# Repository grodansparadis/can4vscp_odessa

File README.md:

<h1>Odessa general CAN4VSCP module</h1>

This module is part of the [VSCP project](https://www.vscp.org).  It is free to use, modify and sell. The only thing we kindly ask is that improvements and extensions are contributed back to the project (at your will). This to make the project better for everyone. All design files is licensed under the [MIT license](https://en.wikipedia.org/wiki/MIT_License).

## Abstract

This document describes the Odessa CAN4VSCP module, its functionality, and usage.
The module is a general-purpose module that connects to a CAN4VSCP bus and can read digital inputs, A/D inputs, and control digital outputs and more. Its functionality is exposed over a 24 pin connector that can be used to connect sensors and actuators.

TRhe module is constructed to be used for custom projects where you need a CAN4VSCP interface to read sensors and control actuators. It can be used in home automation, industrial control, remote monitoring, and more. The module is based on a PIC18F26K83 microcontroller with built-in CAN and A/D converters. It has 8 digital inputs, 4 digital outputs, and 4 A/D inputs. The digital inputs can be used to read switches, buttons, or other digital signals. The digital outputs can be used to control relays, LEDs, or other actuators. The A/D inputs can be used to read analog sensors such as temperature sensors, light sensors, or potentiometers.

Firmware is available that give the module a general I/O functionality. This firmware can be used as a starting point for your own projects.

The module can be attached to a standard DIN Rail or be mounted directly on a wall. 
The module fully adopts to the CAN4VSCP specification and can be powered directly over the bus with a 9-28V DC power source. It has a rich register set for configuration and any information events defined. It also have a decision matrix for easy dynamic event handling.

VSCP CAN modules are designed to work on a VSCP4CAN bus which use ordinary RJ-45 connectors and is powered with 9-30V DC over the same cable. This means there is no need for a separate power cable. All that is needed is a CAT5 or better twisted pair cable. Bus length can be a maximum of 500 meters with drops of maximum 24 meters length (up to a total of 120 meters). As for all VSCP4CAN modules the communication speed is fixed at 125 kbps.

All VSCP modules contains information of there own setup, manual, hardware version, manufacturer etc. You just ask the module for the information you need and you will get it. When they are started up they have a default functionality that often is all that is needed to get a working setup. If the module have something to report it will send you an event and if it is setup to react on a certain type of event it will do it's work when you send event(s) to it.

<hr>

---

## Project files

### User manual
  * [User Manual](https://grodansparadis.github.io/can4vscp-odessa/#)

### Schematic, PCB, 3D files etc
  * [Schematics reversion A](https://github.com/grodansparadis/can4vscp-odessa/blob/master/eagle/odessa_sch_rev_a.png)
  * Hardware design files is made in [KiCad](https://kicad.org) and can be found in the `kicad` directory. Valid from reversion A of the hardware.
  * Gerber files for PCB production can be found in the `gerber` directory (in the `kicad` folder).
  * Eagle schema and board files for reversion A and B can be found in the `eagle` directory. They are no longer actively updated.

 ### Firmware

 The firmware is developed in [MPLAB X IDE](https://www.microchip.com/mplab/mplab-x-ide) using the [XC8 compiler](https://www.microchip.com/mplab/compilers).

  * Binary release files is available [here](https://github.com/grodansparadis/can4vscp-odessa/releases)

### MDF - Module Description File(s)
  * [MDF file version: 1 Release date: 2020-05-15](http://www.eurosource.se/odessa001.xml)

### Support
If you need support, please open an issue in the [GitHub repository](https://github.com/grodansparadis/can4vscp-odessa/issues).

### Buy a ready made modules
You can buy a ready made module from [Grodans Paradis](http://www.grodansparadis.com).

### Project related links
  * [VSCP project](https://www.vscp.org)
  * [VSCP Documentation site](https://docs.vscp.org/)
  * [VSCP Wiki](https://github.com/grodansparadis/vscp/wiki)

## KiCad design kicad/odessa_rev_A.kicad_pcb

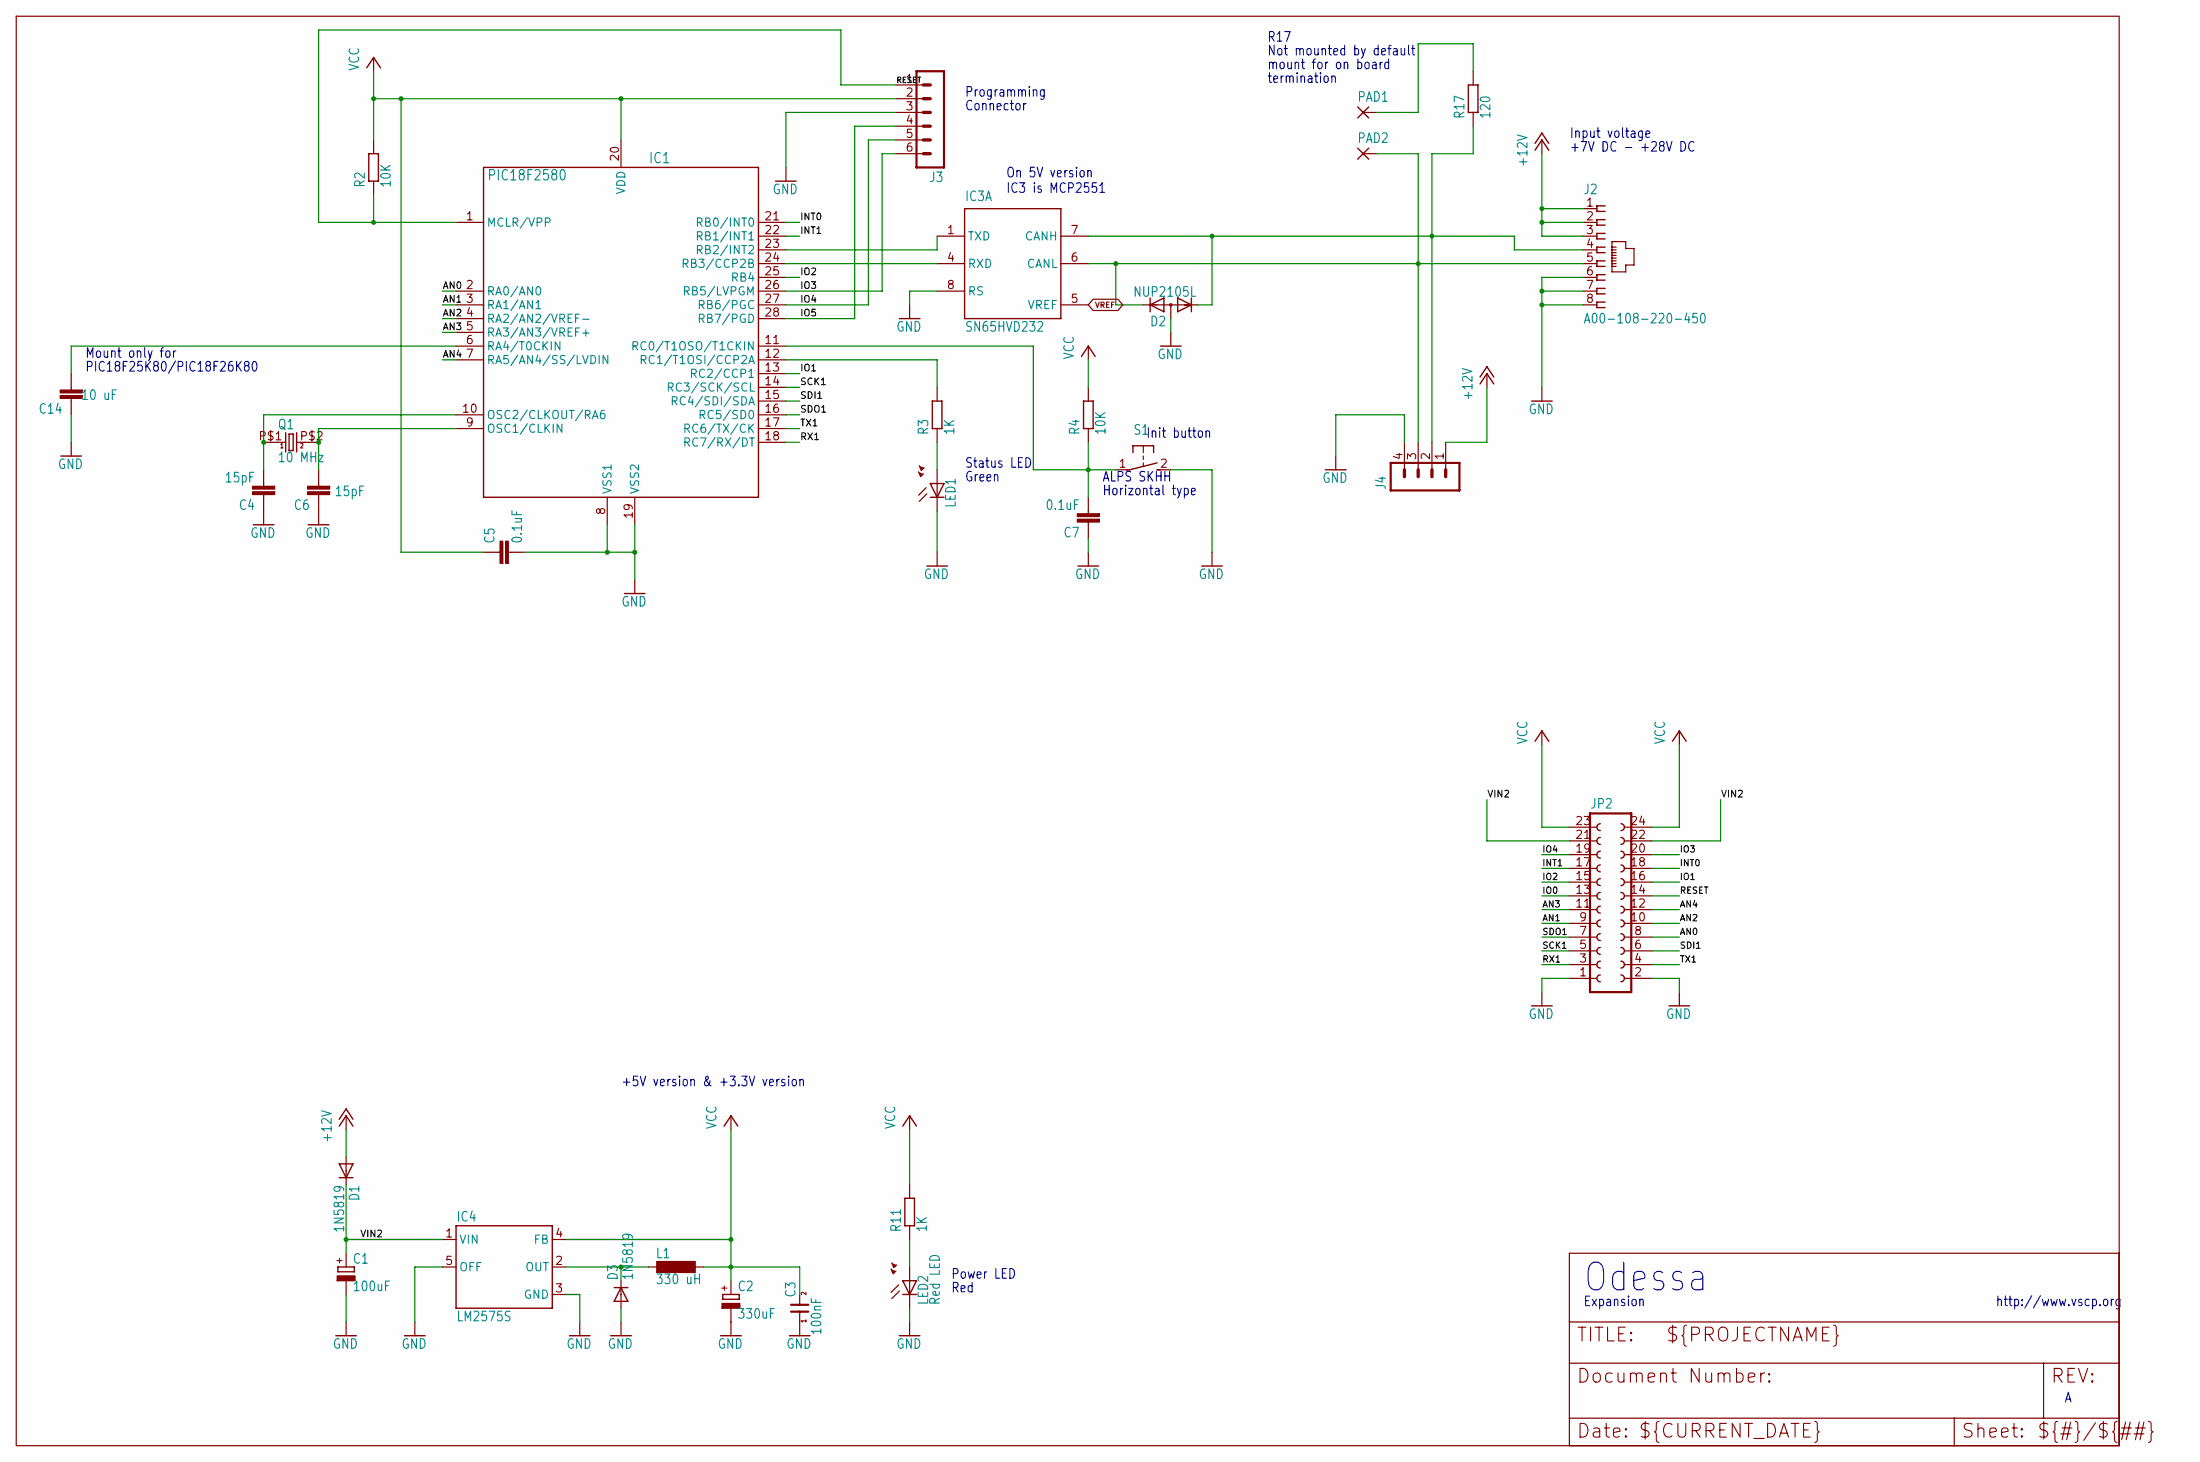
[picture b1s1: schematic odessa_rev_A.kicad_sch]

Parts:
C1: 100uF; PANASONIC_D
C2: 330uF; PANASONIC_D
C3: 100nF; 0805
C4, C6: 15pF; C0805
C5, C7: 0.1uF; C0805
C14: 10 uF; C0805
D1, D3: 1N5819; SOD123
D2: NUP2105L; SOT23
IC1: PIC18F2580; SO28
IC3: SN65HVD232; SO-08
IC4: LM2575S; TO263-5
J2: A00-108-220-450; RJ-45
J3: MA06-1
J4: MA04-1
JP2: FE12-2
L1: 330 uH; DO3316P
LED1: LEDCHIP-LED0805; CHIP-LED0805
LED2: Red LED; CHIP-LED0805
PAD1, PAD2: 1,6/0,8; 1,6_0,8
Q1: 10 MHz; 9C
R2, R4: 10K; R0805
R3, R11: 1K; R0805
R17: 120; R0805
S1: 31-XX; B3F-31XX

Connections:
+12V: D1.A, J2.1, J2.2, J2.3, J4.1
AN0: IC1.2 (RA0/AN0), JP2.8
AN1: IC1.3 (RA1/AN1), JP2.9
AN2: IC1.4 (RA2/AN2/VREF-), JP2.10
AN3: IC1.5 (RA3/AN3/VREF+), JP2.11
AN4: IC1.7 (RA5/AN4/SS/LVDIN), JP2.12
CANL: D2.2 (K2), IC3.6 (CANL), J2.5, J4.3, PAD2.1
GND: C1.-, C2.-, C3.1, C4.1, C5.2, C6.1, C7.1, C14.1, D2.3 (A), D3.A, IC1.8 (VSS1), IC1.19 (VSS2), IC3.2 (VSS), IC3.8 (RS), IC4.3 (GND), IC4.5 (OFF), J2.6, J2.7, J2.8, J3.3, J4.4, JP2.1, JP2.2, LED1.C, LED2.C, S1.2 (S)
INT0: IC1.21 (RB0/INT0), JP2.18
INT1: IC1.22 (RB1/INT1), JP2.17
IO0: JP2.13
IO1: IC1.13 (RC2/CCP1), JP2.16
IO2: IC1.25 (RB4), JP2.15
IO3: IC1.26 (RB5/LVPGM), J3.6, JP2.20
IO4: IC1.27 (RB6/PGC), J3.5, JP2.19
IO5: IC1.28 (RB7/PGD), J3.4
unnamed: D3.C, IC4.2 (OUT), L1.1
unnamed: C4.2, IC1.10 (OSC2/CLKOUT/RA6), Q1.P$1 (1)
unnamed: C14.2, IC1.6 (RA4/T0CKIN)
unnamed: IC1.12 (RC1/T1OSI/CCP2A), R3.2
unnamed: LED1.A, R3.1
unnamed: C7.2, IC1.11 (RC0/T1OSO/T1CKIN), R4.1, S1.1
unnamed: C6.2, IC1.9 (OSC1/CLKIN), Q1.P$2 (2)
unnamed: PAD1.1, R17.2
unnamed: LED2.A, R11.1
unnamed: D2.1 (K1), IC3.7 (CANH), J2.4, J4.2, R17.1
RESET: IC1.1 (MCLR/VPP), J3.1, JP2.14, R2.1
RX1: IC1.18 (RC7/RX/DT), JP2.3
RXCAN: IC1.24 (RB3/CCP2B), IC3.4 (RXD)
SCK1: IC1.14 (RC3/SCK/SCL), JP2.5
SDI1: IC1.15 (RC4/SDI/SDA), JP2.6
SDO1: IC1.16 (RC5/SD0), JP2.7
TX1: IC1.17 (RC6/TX/CK), JP2.4
TXCAN: IC1.23 (RB2/INT2), IC3.1 (TXD)
VCC: C2.+, C3.2, C5.1, IC1.20 (VDD), IC3.3 (VDD), IC4.4 (FB), J3.2, JP2.23, JP2.24, L1.2, R2.2, R4.2, R11.2
VIN2: C1.+, D1.C, IC4.1 (VIN), JP2.21, JP2.22
VREF: IC3.5 (VREF)

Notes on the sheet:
Red
Green
Not mounted by default
Odessa
Init button
Horizontal type
Power LED
Input voltage
On 5V version IC3 is MCP2551
+7V DC - +28V DC
R17
http://www.vscp.org
termination
mount for on board
Status LED
ALPS SKHH
Connector
PIC18F25K80/PIC18F26K80
Programming
Mount only for
+5V version & +3.3V version
Expansion

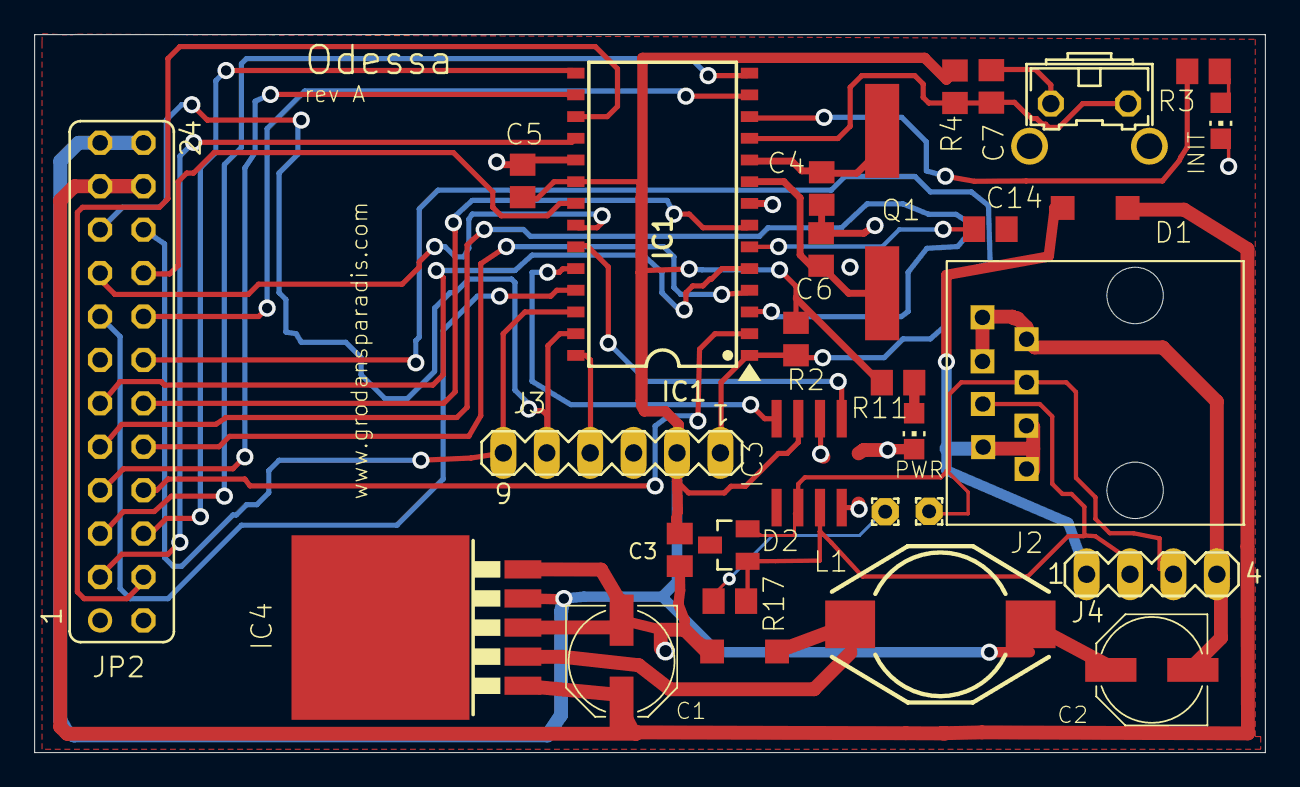
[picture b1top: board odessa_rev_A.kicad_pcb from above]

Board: 6 copper layers, 72.0 x 42.0 mm, 30 parts (0 on the bottom side), 35 nets.

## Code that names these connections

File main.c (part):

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#pragma config BORV  = 0        // 3V

// CONFIG3H
#pragma config CANMX = PORTB    // ECAN TX and RX pins are located on RB2 and RB3, respectively.
#pragma config MSSPMSK = MSK7   // 7 Bit address masking mode.
#pragma config MCLRE = ON       // MCLR Enabled, RE3 Disabled.

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    switch ( param ) {
        
        case 3:
            PORTCbits.RC7 = 1;
            break;
       
        case 4:
            PORTCbits.RC6 = 1;
            break;
            
        case 5:
            PORTCbits.RC3 = 1;
            break;
            
        case 6:
            PORTCbits.RC4 = 1;
            break;
            
        case 7:
            PORTCbits.RC5 = 1;
            break;
            
        case 8:
            PORTAbits.RA0 = 1;
            break;
            
        case 9:
            PORTAbits.RA1 = 1;
            break;
            
        case 10:
            PORTAbits.RA2 = 1;
            break;
            
        case 11:
            PORTAbits.RA3 = 1;
            break;
            
        case 12:
            PORTAbits.RA5 = 1;
            break;
            
        case 13:
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            break;
            
        case 15:
            PORTBbits.RB4 = 1;
            break;
            
        case 16:
            PORTCbits.RC2 = 1;
            break;
            
        case 17:
            PORTBbits.RB1 = 1;
            break;
        
        case 18:
            PORTBbits.RB0 = 1;
            break;
            
        case 19:
            PORTBbits.RB6 = 1;
            break;
            
        case 20:
            PORTBbits.RB5 = 1;
            break;            
                        
    }
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    switch ( param ) {
        
        case 3:
            PORTCbits.RC7 = 0;
            break;
       
        case 4:
            PORTCbits.RC6 = 0;
            break;
            
        case 5:
            PORTCbits.RC3 = 0;
            break;
            
        case 6:
            PORTCbits.RC4 = 0;
            break;
            
        case 7:
            PORTCbits.RC5 = 0;
            break;
            
        case 8:
            PORTAbits.RA0 = 0;
            break;
            
        case 9:
            PORTAbits.RA1 = 0;
            break;
            
        case 10:
            PORTAbits.RA2 = 0;
            break;
            
        case 11:
            PORTAbits.RA3 = 0;
            break;
            
        case 12:
            PORTAbits.RA5 = 0;
            break;
            
        case 13:
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            break;
            
        case 15:
            PORTBbits.RB4 = 0;
            break;
            
        case 16:
            PORTCbits.RC2 = 0;
            break;
            
        case 17:
            PORTBbits.RB1 = 0;
            break;
        
        case 18:
            PORTBbits.RB0 = 0;
            break;
            
        case 19:
            PORTBbits.RB6 = 0;
            break;
            
        case 20:
            PORTBbits.RB5 = 0;
            break;            
                        
    }
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
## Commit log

2015-04-19 Initial check in
2015-04-22 Code in place
2015-04-23 All tested except decision matrix
2015-04-24 Version 1.0.0
2015-04-24 relocated compile
2015-06-24 Using peripheral eeprom functions now
2015-07-11 Added hex files
2015-07-27 Fixed problem with send timeout
2015-08-17 Changed license to Artistic License 3.0
2015-08-23 Added schema
2015-11-13 Added firmware readme
2015-11-17 Reported decision matrix info was wrong. Fixed
2015-12-07 Edit
2015-12-17 Updated license
2015-12-17 Changed copyright info in headers so it is correct
2015-12-22 Added to ignores
2016-03-08 Now compiles with firmware 1.6
2016-03-08 Updated copyright information
2016-03-23 Fixed bug in control byte write routine
2016-03-23 Adopted to VSCP firmware 1.6.1
2016-03-23 Noted version
2016-03-23 Renamed
2016-03-23 Version 1.0.2
2016-04-19 Brwn out now ar 3V
2016-05-04 Added new link to bit timing
2020-05-15 init timer is noe 2500 ms
2020-05-15 Updated firmware
2025-08-18 Converted schema to kicad
2025-09-23 Files modified for now nameing convention
2025-09-23 Added folder for design documents
2025-09-25 Expansion updated
2025-09-30 Changed license to MIT
2025-09-30 Start translation of manual
2025-09-30 Added tema
2025-09-30 Added images from wiki
2025-09-30 Renamed register description file
2025-09-30 Added missing files
2025-09-30 Testing register rendering
2025-09-30 test rendering
2025-09-30 Added folder for register sets
2025-09-30 Added VSCP logo
2025-09-30 Formating
2025-09-30 Formatting
2025-09-30 Cleaned up

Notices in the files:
main.c:
Copyright (C)1995-2020 Ake Hedman, Grodans Paradis AB
This work is licensed under the Creative Common
http://creativecommons.org/licenses/by-nc-sa/3.0/legalcode
http://creativecommons.org/licenses/by-nc-sa/3.0
